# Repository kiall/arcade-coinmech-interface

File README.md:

# Arcade Coin Mechanism Interface

This is a simple little interface board to connect a 12V arcade coin mechanism to a 5V interface board (e.g. the Ultimarc I-Pac). The board supports connecting 2x 12V coin mechanism, and 1x 12V Coin Counter.

# So - Where to get one?

I don't sell these! The design is Open Source. I upload my designs to OSH Park and have them manafacture the board for me, I've included a link below.

(I do not earn commission etc from OSH Park if you order from them)

# But, What does it look like?

# What parts will I need?

1. The PCB itself (See below)
2. 2x JST-XH 4 pin sockets
3. 2x JST-XH 2 pin sockets
4. 1x JST-XH 2 pin sockets
5. 2x 5V Zener Diodes

I use JST-XH sockets everywhere, but any socket with a 2.54mm pitch and approximatly the same outside will do just fine.

# How do I assemble it?

1. Place the 2x Zener Diodes into their spots (D1 and D2) and solder in place. Ensure the stripe on the diode is on the correct side - match the orientation shown on the PCB itself.
2. Place the JST-XH connectors.
   1. Pay attention to the orientation, the markings on the PCB show which direction the socket should go, look at the slots in the connector. If using a different connector type, just be consistent in which way you orient the connectors!
   2. Place all connectors at once, then carefully turn the board upside down and allow it to rest on the connectors.
   3. Solder all the pins.
3. Your done assembling the board!

# What wiring is needed?

## Coin Mechanism 1 & 2 Sockets - J2 & J3

* Pin 1 (Square Pad): Coin Mech "Counter" wire.
* Pin 2: Coin Mech "Ground" wire.
* Pin 2: Coin Mech "Coin" wire.
* Pin 4: Coin Mech "12V" wire.

## Counter Socket - J5

*Generally, the wires on a coin counter are identical and it doesn't actually matter which way around you wire them.*

* Pin 1 (Square Pad): Coin Counter 12V Supply
* Pin 2: Coin Counter Increment Signal

## KB Enc Socket - J4

* Pin 1 (Square Pad): Keyboard Encoder Ground (e.g. I-PAC Ground Loop)
* Pin 2: Keyboard Encoder Coin 1 Input
* Pin 3: Keyboard Encoder Coin 2 Input

## Power Input Socket - J1

* Pin 1 (Square Pad): 12V from Power Supply
* Pin 2: Ground from Power Supply

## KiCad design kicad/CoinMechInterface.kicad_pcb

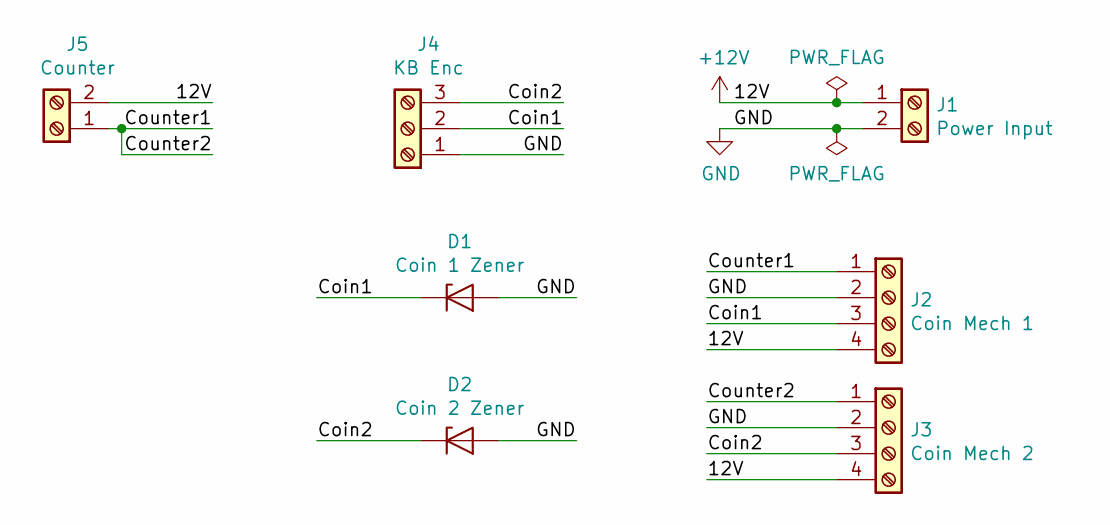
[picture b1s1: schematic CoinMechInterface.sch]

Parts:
D1: Coin 1 Zener; D_T-1_P5.08mm_Horizontal
D2: Coin 2 Zener; D_T-1_P5.08mm_Horizontal
J1: Power Input; JST_XH_B02B-XH-A_1x02_P2.50mm_Vertical
J2: Coin Mech 1; JST_XH_B04B-XH-A_1x04_P2.50mm_Vertical
J3: Coin Mech 2; JST_XH_B04B-XH-A_1x04_P2.50mm_Vertical
J4: KB Enc; JST_XH_B03B-XH-A_1x03_P2.50mm_Vertical
J5: Counter; JST_XH_B02B-XH-A_1x02_P2.50mm_Vertical

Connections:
+12V: J1.1, J2.4, J3.4, J5.2
/Coin1: D1.1 (K), J2.3, J4.2
/Coin2: D2.1 (K), J3.3, J4.3
/Counter1: J2.1, J3.1, J5.1
GND: D1.2 (A), D2.2 (A), J1.2, J2.2, J3.2, J4.1

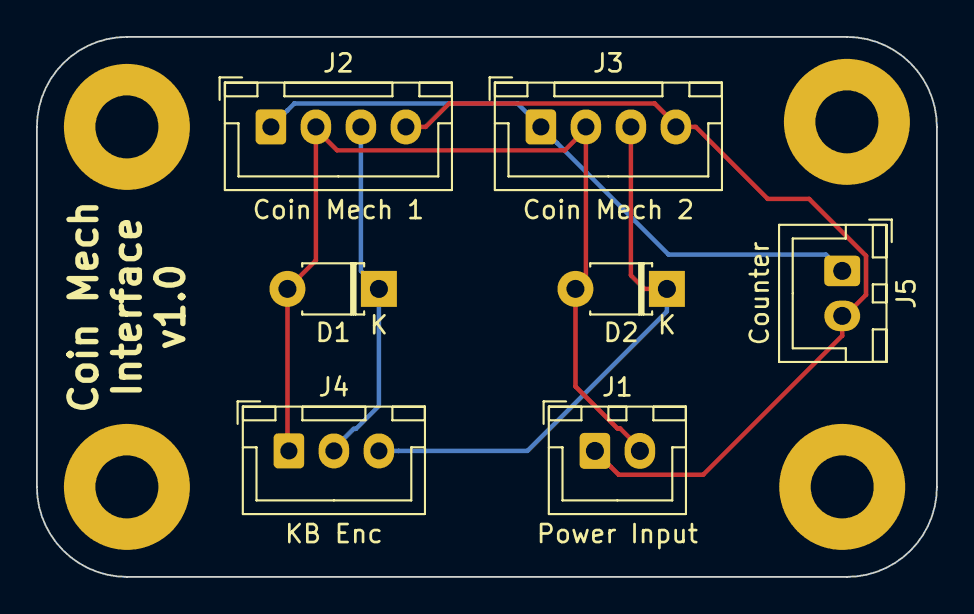
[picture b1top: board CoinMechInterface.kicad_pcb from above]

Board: 2 copper layers, 50.0 x 30.0 mm, 7 parts (0 on the bottom side), 5 nets.

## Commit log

2019-07-07 Fix README
2019-07-07 Add images
2019-07-07 Add photos
2019-07-07 Add LICENSE
